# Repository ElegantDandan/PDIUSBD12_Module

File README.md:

# PDIUSBD12_Module

本模块是根据《圈圈教你玩USB》书中学习板提取设计而来，完全兼容书中学习板，使用本模块可使广大USB学者不再受限于STC89C52RC单片机。

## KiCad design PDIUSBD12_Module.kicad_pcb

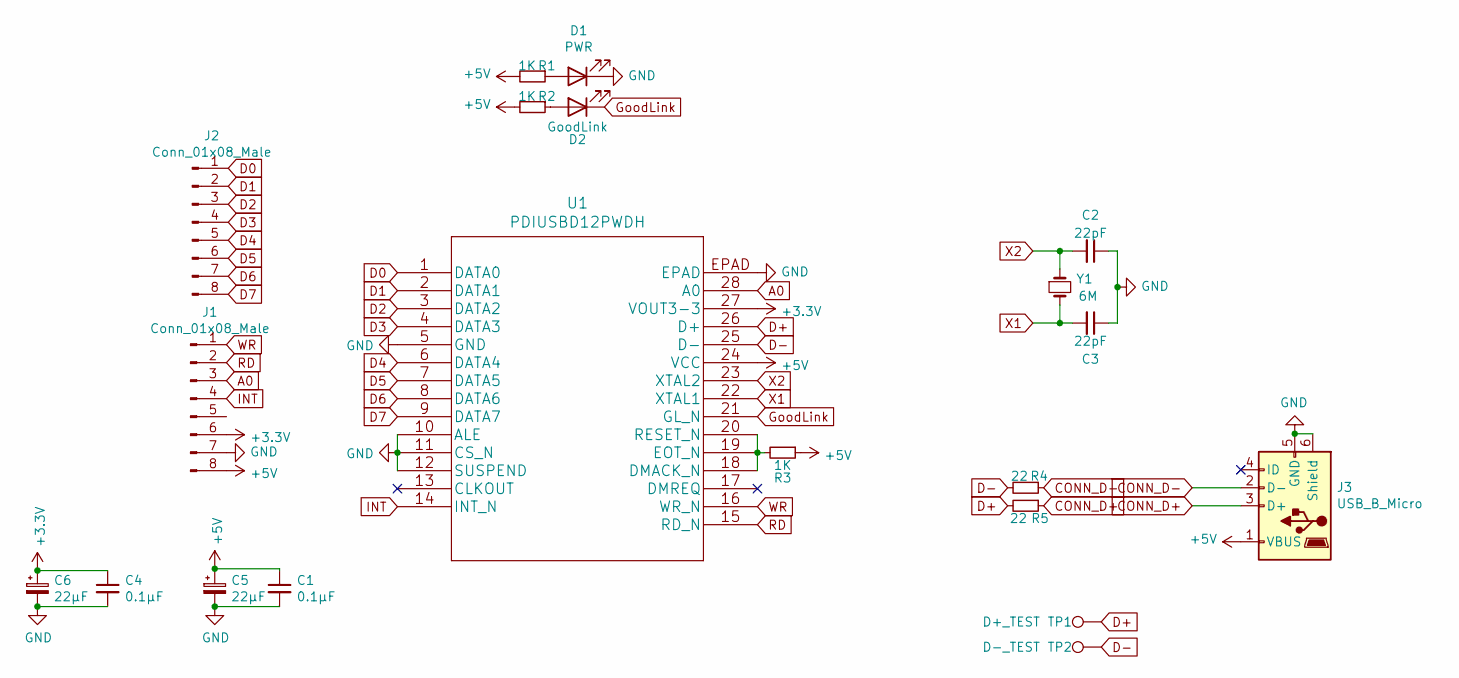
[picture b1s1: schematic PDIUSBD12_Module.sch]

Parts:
C1, C4: 0.1μF; C_0603_1608Metric_Pad1.08x0.95mm_HandSolder
C2, C3: 22pF; C_0603_1608Metric_Pad1.08x0.95mm_HandSolder
C5, C6: 22μF; CP_Elec_4x5.4
D1: PWR; LED_0603_1608Metric_Pad1.05x0.95mm_HandSolder
D2: GoodLink; LED_0603_1608Metric_Pad1.05x0.95mm_HandSolder
J1, J2: Conn_01x08_Male; PinHeader_1x08_P2.54mm_Vertical
J3: USB_B_Micro; USB_Micro-B_Wuerth_629105150521
R1, R2, R3: 1K; R_0603_1608Metric_Pad0.98x0.95mm_HandSolder
R4, R5: 22; R_0603_1608Metric_Pad0.98x0.95mm_HandSolder
TP1: D+_TEST; TestPoint_Pad_D1.5mm
TP2: D-_TEST; TestPoint_Pad_D1.5mm
U1: PDIUSBD12PWDH
Y1: 6M; Crystal_HC49-4H_Vertical

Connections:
+3V3: C4.1, C6.1, J1.6, U1.27 (VOUT3-3)
+5V: C1.1, C5.1, J1.8, J3.1 (VBUS), R1.2, R2.2, R3.1, U1.24 (VCC)
A0: J1.3, U1.28 (A0)
CONN_D+: J3.3 (D+), R5.1
CONN_D-: J3.2 (D-), R4.1
D0: J2.1, U1.1 (DATA0)
D1: J2.2, U1.2 (DATA1)
D2: J2.3, U1.3 (DATA2)
D3: J2.4, U1.4 (DATA3)
D4: J2.5, U1.6 (DATA4)
D5: J2.6, U1.7 (DATA5)
D6: J2.7, U1.8 (DATA6)
D7: J2.8, U1.9 (DATA7)
D+: R5.2, TP1.1, U1.26 (D+)
D-: R4.2, TP2.1, U1.25 (D-)
GND: C1.2, C2.1, C3.1, C4.2, C5.2, C6.2, D1.1 (K), J1.7, J3.5 (GND), J3.6 (Shield), U1.5 (GND), U1.10 (ALE), U1.11 (CS_N), U1.12 (SUSPEND), U1.EPAD
GoodLink: D2.1 (K), U1.21 (GL_N)
INT: J1.4, U1.14 (INT_N)
unnamed: D1.2 (A), R1.1
unnamed: D2.2 (A), R2.1
unnamed: R3.2, U1.18 (DMACK_N), U1.19 (EOT_N), U1.20 (RESET_N)
RD: J1.2, U1.15 (RD_N)
WR: J1.1, U1.16 (WR_N)
X1: C3.2, U1.22 (XTAL1), Y1.2
X2: C2.2, U1.23 (XTAL2), Y1.1

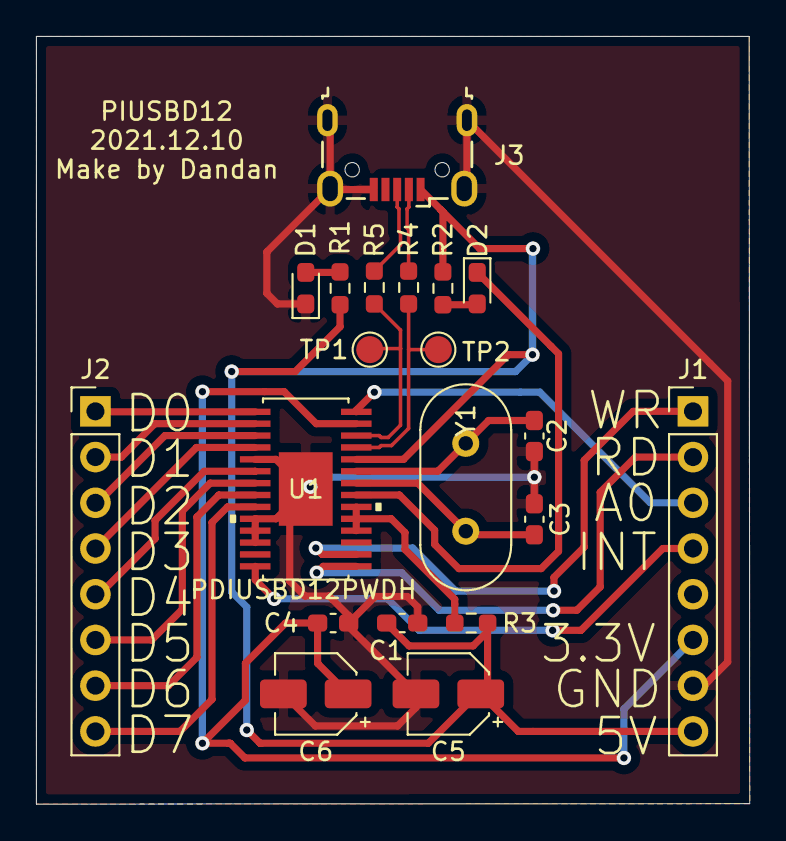
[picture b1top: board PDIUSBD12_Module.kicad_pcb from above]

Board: 2 copper layers, 39.6 x 42.6 mm, 20 parts (0 on the bottom side), 25 nets.

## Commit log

2021-12-10 add readme

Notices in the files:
parts and their libraries:
Copyright 2021 Accelerated Designs. All rights reserved.
